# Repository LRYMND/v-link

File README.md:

## Welcome to the Boosted Moose V-Link project!

Let's face it. MMIs from the 2000s suck. This is a personal project that I started because I couldn't find a suitable aftermarket solution. I wanted to implement live vehicle data as well as AndroidAuto/Apple CarPlay in an OEM like fashion to enhance the driving experience of retro cars and give the user the ability to tinker around. The heart of this project is the open source V-Link app. It's running natively on Raspberry Pi OS which enables full support of an OS without the restrictions of 3rd party images. A custom made HAT builds the bridge between the Raspberry Pi and the car and works plug and play with the app.

To use this application you need a Raspberry Pi, the V-Link Hat (optional) and an HDMI-screen, preferably with touch support.

This project is in ongoing development. Do you want to participate, got any tips for improvement or need help?

* [Swedespeed Forum](https://www.swedespeed.com/threads/volvo-rtvi-raspberry-media-can-interface.658254/)
* [V-Link Discord Server](https://discord.gg/V4RQG6p8vM)

Feel free to fork the project. Create a new branch, commit your changes and open a pull request.

## Content

<!-- TABLE OF CONTENTS -->
<details open="open">
  <summary>Table of Contents</summary>
  <ol>
    <li><a>| App Installation</a></li>
    <li><a>| HAT Setup</a></li>
    <li><a>| Display Mod</a></li>
    <li><a>| Wiring</a></li>
    <li><a>| Audio</a></li>
    <li><a>| Disclaimer</a></li>
    <li><a>| Known Issues</a></li>
    <li><a>| Roadmap</a></li>
  </ol>
</details>

---

## 01 | App Installation

### > System Requirements:
```
Running on Raspberry Pi 3/4/5
Raspberry Pi OS 12 (Bookworm)
```

For the best user experience a RPi 4 or 5 is recommended.

---

### > Run the App:

When using the Installer everything is being set up automatically.
Before updating, please uninstall the app. (See below)

```
#Download and Install
wget "https://github.com/LRYMND/v-link/releases/download/v2.2.1/Installer.sh"
sudo chmod +x Installer.sh
sudo ./Installer.sh

#Test Hardware (Requires V-Link HAT)
python /home/$USER/v-link/HWT.py

#Execute
python /home/$USER/v-link/V-Link.py

#Advanced Options:
python /home/$USER/v-link/V-Link.py -h
```

#### In case you get an error when installing the requirements run these commands:
```
source /home/$USER/v-link/venv/bin/activate
pip install -r /home/$USER/v-link/requirements.txt
```
---

### > Run as Developer:
```
git clone https://github.com/lrymnd/v-link.git
cd v-link
python -m venv venv
source /home/$USER/v-link/venv/bin/activate
pip install -r requirements.txt
cd frontend
npm i & npm run build

cd /home/$USER/v-link/frontend
npm run vite

cd /home/$USER/v-link
python V-Link.py -h
```

```
Node v18.12.1
NPM 8.19.2
```

### > Uninstall:
```
cd ~/home/$USER/v-link/
sudo chmod +x Uninstall.sh
./Uninstall.sh
```

The Uninstall.sh script removes entries from the following location. However this is only supported from 2.2.0 onwards.
Earlier installations need to be removed manually.

```
/etc/udev/rules.d/
/etc/xdg/autostart/
/etc/network/interfaces
/home/$USER/.config
/boot/firmware/config.txt
/etc/systemd/system/
/etc/sudoers.d/
```

### > Additional functionality:

CAN and ADC data can be recorded from the chart dashboard. This data can be downloaded and evaluated with plotter.py from the /resources/tools/ folder.

```
python plotter.py $PATH_TO_JSON
```

#### Entries in /boot/firmware/config.txt:

```
[V-LINK RPi3]

#Enable GPIO 0&1
disable_poe_fan=1
force_eeprom_read=0

#Enable devicetree overlays
dtoverlay=disable-bt
enable_uart=1

dtparam=i2c_arm=on
dtoverlay=v-link
dtoverlay=mcp2515-can1,oscillator=16000000,interrupt=24
dtoverlay=mcp2515-can2,oscillator=16000000,interrupt=22

#Configure IGN logic
dtoverlay=gpio-shutdown,active_low=0,gpio_pull=up,gpio_pin=1
dtoverlay=gpio-poweroff,gpiopin=0

#No Splash on boot
disable_splash=1
```

```
[V-LINK RPi4]

#Enable GPIO 0&1
disable_poe_fan=1
force_eeprom_read=0

#Enable devicetree overlays
dtparam=spi=on
enable_uart=1
dtparam=i2c_arm=on

dtoverlay=v-link
dtoverlay=uart3
dtoverlay=mcp2515-can1,oscillator=16000000,interrupt=24
dtoverlay=mcp2515-can2,oscillator=16000000,interrupt=22

#Configure IGN logic
dtoverlay=gpio-shutdown,active_low=0,gpio_pull=up,gpio_pin=1
dtoverlay=gpio-poweroff,gpiopin=0

#No Splash on boot
disable_splash=1
```

```
[V-LINK RPi5]

#Enable GPIO 0&1
disable_poe_fan=1
force_eeprom_read=0

#Enable devicetree overlays
dtparam=spi=on
enable_uart=1
dtparam=i2c_arm=on

dtoverlay=v-link
dtparam=uart0=on
dtoverlay=uart2-pi5
dtoverlay=mcp2515-can1,oscillator=16000000,interrupt=24
dtoverlay=mcp2515-can2,oscillator=16000000,interrupt=22

#Configure IGN logic
dtoverlay=gpio-shutdown,active_low=0,gpio_pull=up,gpio_pin=1
dtoverlay=gpio-poweroff,gpiopin=0

#No Splash on boot
disable_splash=1
```
*(Don't forget to copy the custom overlays from the devicetree folder of this repository to /boot/firmware/overlays!)*

#### Further Setup:

When installing everything manually you need to set up certain features. Below you can find a list of commands to enable all necessary ports and access rights:

Enabling CAN:
```
sudo ip link set can1 type can bitrate 500000
sudo ip link set up can1

sudo ip link set can2 type can bitrate 125000
sudo ip link set up can2
```

Enabling uinput & vcan:
```
sudo modprobe uinput
sudo modprobe vcan
```

Rules for /etc/udev/rules.d/42-v-link.rules:
```
SUBSYSTEM=="usb", ATTR{idVendor}=="1314", ATTR{idProduct}=="152*", MODE="0660", GROUP="plugdev"
KERNEL=="ttyS0", MODE="0660", GROUP="plugdev"
KERNEL=="uinput", MODE="0660", GROUP="plugdev"
```

## 02 | HAT Setup

Here you can find a list of the required hardware. The V-Link HAT is currently only being sold in small batches to interested ones. If you are interested in how to get one I encourage you getting in contact via Discord! The old method which involved more hardware and technical skill is archived in the 2.0.0 branch of this repo. 

#### Hardware:
- V-Link HAT
- Raspberry Pi 3/4/5
- OEM P1 RTI Display Unit
- Carlinkit Adapter

##### CarPlay / AndroidAuto:
As of now, Carplay is working reliably on the CPC200-CCPA while AndroidAuto works better on the CPC200-CCPM Dongle. In theory, Android Auto should work on the CCPA version as well but we had mixed results. Keep this in mind when choosing your Carlinkit Adapter.

##### Raspberry Pi 3:
The Raspberry Pi 3 comes with only two UART ports. In order to use the RTI functionality you will need to place a jumper between GPIO4 and GPIO14 and short them together. Your GPIO pins won't be damaged through this and the signal arrives at the terminal of the HAT.

The V-Link HAT is attached to the Raspberry and builds the interface to the car. On this PCB you have terminals to hook up 12V, IGN, CAN etc. It also implements a safe shutdown functionality which gracefully turns off the Raspberry once ignition is off. In this state it draws a minimum of current so draining your cars battery won‘t be an issue. The LCD Touch Display and the Carlinkit Adapter are plugged into the HDMI / USB port of the raspberry and complete the setup.

## 03 | Display Mod

We currently investigate the possibility of using the OEM LCD unit, however it's recommended to go the extra mile as the proposed display has a much better resolution and supports touch input with an additional panel. The HAT comes with a dedicated 5V pin on the power terminal to run the LCD.

* [LCD Driver](https://de.aliexpress.com/item/4001175095149.html?spm=a2g0o.order_list.0.0.30e65c5fXw0Aa6&gatewayAdapt=glo2deu)
* [LCD Display](https://de.aliexpress.com/item/32835602509.html?spm=a2g0o.order_list.0.0.30e65c5fXw0Aa6&gatewayAdapt=glo2deu)
* [6.5" Touch Screen Module](https://www.ebay.de/itm/170981315406)

In order to mod your display you need to disassemble the case and take the OEM components out. Afterwards mount the new Screen in place. A custom 3D-printable bracket for easy installation can be found in the /resources folder. Be aware that the the LCDs from aliexpress come in different thicknesses. Unfortunately you can't really determine which one you're getting but if you have the option go for the slimmest variant.

## 04 | Wiring

### > 4.1 Main Connections

One way to connect the HAT to the car is to wire it to the CEM. You can solder - or better re-crimp - the wires directly to the connector. That way you aren't splicing any harnesses and the mod can be undone without damaging anything. The idea is to have an additional harness to the HAT. Keep in mind to choose appropriate diameters for you wire so they can carry the load and still fit in the connector. This is especially critical with the CAN wiring. In the future we want to make this a bit more easy.

(Borrowed from the original Volvo Electronic Wiring Diagrams)

The connections below are the bare minimum for the app to function properly on the Volvo P1 platform:

```
| Connection  | CEM Connector | Pin | HAT     |
| ----------- | ------------- | --- | ------- |
| CAN-H HS    | B             | 11  | CAN 1 H |
| CAN-L HS    | B             | 12  | CAN 1 L |
| GND         | A             | 28  | GND     |
| IGN         | A             | 17  | IGN     |
| 12V         | E             | 21  | VBAT    |
```

### > 4.2 Steering Wheel Controls (WIP)

In order to implement the steering wheel controls, you need to connect the HAT to the LIN bus of your car. The app will convert the signals from the steering wheel buttons to keyboard/mouse HID events. The easiest place to find the LIN Bus is the "ICM Connector A" behind the waterfall. Disassemble the ICM and solder a small wire to it as shown in the picture below, or add a small wire to the ICM's wiring harness.

#### Control folding mechanism:
```
| Button  | Function                  |
| ------- | ------------------------- |
| 'back'  | Hold down to close screen |
| 'enter' | Click to open screen      |
```
#### Control interface:
```
| Button     | Normal Mode | Mouse Mode         |
| ---------- | ----------- | ------------------ |
| 'Enter'    | Enter       | Left Click         |
| 'Joystick' | Navigate    | Control mouse      |
```

Holding down `Enter` button for ~2 seconds toggles between normal and mouse mode. The button mappings can be adjusted in the app.

---

### > 4.3 RTI folding mechanism

Connect Pin 4 from the RTI to the RTI pin of the HAT. You can solder directly to the RTI PCB/connector, or you can plug a DuPont wire into the connector. This can be done on the RTI side of the cable, or on the other side of the cable in the glove box. 

When ignition is turned on, the RTI screen automatically folds up. You can fold it back down through the app or the dedicated steering wheel button. Keep in mind, if your steering wheel module is not connected, you will not be able to bring the screen back up without restarting your car. The LCD will be automatically turned off in the hidden state to save power.

---

### > 4.4 Additonal Peripherals

The HAT has an input for up to 4 analog sensors. A preconfigured settings file for the Bosch 0261230482 sensor kit is provided and enables temperature and pressure readings in the app. The settings file for the analogue sensors are exposed like the CAN settings, so sensors can be added without making any changes to the code at all.

Also, to make life a bit easier, you can connect an USB extension cable to the Raspi and mount it to the removable tray behind the waterfall console. This way you can directly connect peripherals to it.

## 05 | Audio

The current solution for getting audio to work in cars that don't have a factory aux port is a [small module](https://www.tindie.com/products/justtech/aux-input-volvo-v50-s40-c30-c70-xc90/) from Lithuania.
This module is a mod for the radio to add an aux port. There is also a Bluetooth version available but since the phone is already wirelessly connected to the Carlinkit adapter dongle, an aux-cable seems pretty clean and less prone to failure.

### > Note:

This is no advertisement, just a clean and simple solution IMO. And since MOST-Bus is supported through the PiMost from ModernDayMods, it might be possible to send audio over the MOST network in the future. This is still under investigation. Feel free to join the Discord Server if you want to participate in development.

## 06 | Disclaimer

The use of this soft- and hardware is at your own risk. The author and distributor of this project is not responsible for any damage, personal injury, or any other loss resulting from the use or misuse of the setup described above. By using this setup, you agree to accept full responsibility for any consequences that arise from its use. It’s DIY after all!

## 07 | Known Issues

- In a few cases, CarPlay will connect but the stream is not visible. Restarting carplay on the phone resolves this.
- In a few cases, CAN bus communication is not working right away. Restarting the app resolves this.

## 08 | Roadmap

- [x] Exposed setting files
- [x] Fully responsive UI
- [x] Implement LIN
- [x] Implement ADC
- [x] Implement RTI
- [x] Custom hardware interface
- [x] 3D-printed display mount
- [ ] Preconfiguration for different engines
- [ ] Improved wiring to the car
- [ ] Implement DTCs
- [ ] Implement MOST

---
#### The project is inspired by the following repositories:

* [volvo-can-gauge](https://github.com/Alfaa123/Volvo-CAN-Gauge)
* [react-carplay](https://github.com/rhysmorgan134/react-carplay)
* [volvo-crankshaft](https://github.com/laurynas/volvo_crankshaft)
* [volve](https://github.com/LuukEsselbrugge/Volve)
* [volvo-vida](https://github.com/Tigo2000/Volvo-VIDA)

#### Want to join development, got any tips for improvement or need help?  

* [Swedespeed Forum](https://www.swedespeed.com/threads/volvo-rtvi-raspberry-media-can-interface.658254/)
* [V-Link Discord Server](https://discord.gg/V4RQG6p8vM)

---

|   |  |
|---|---|
| <center>(Louis)</center> | <center>(Tigo)</center> |

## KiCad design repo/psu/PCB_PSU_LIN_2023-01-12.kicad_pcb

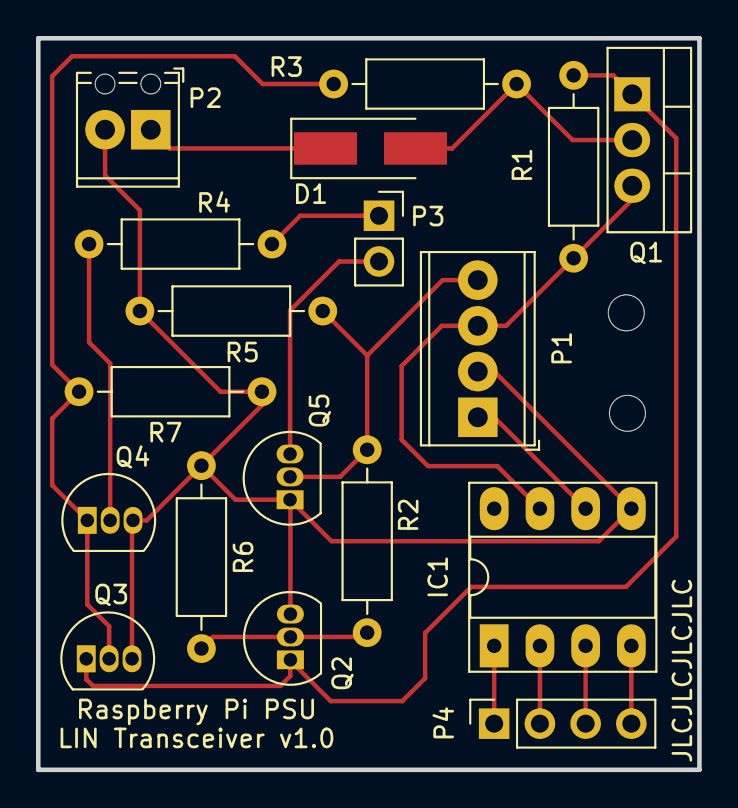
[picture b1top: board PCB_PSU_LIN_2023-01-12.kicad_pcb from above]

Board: 2 copper layers, 36.7 x 40.6 mm, 18 parts (0 on the bottom side), 12 nets.

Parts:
D1: D1; D_SMA_Handsoldering
IC1: MCP2004-E/P LIN Transceiver, 20Kbaud, Dip-8 Micro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; DIP-8_W7.62mm_Socket_LongPads
P1: TerminalBlock_Phoenix_MPT-0,5-4-2.54_1x04_P2.54mm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; TerminalBlock_Phoenix_MPT-0,5-4-2.54_1x04_P2.54mm_Horizontal
P2: TerminalBlock_Phoenix_MPT-0,5-2-2.54_1x02_P2.54mm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; TerminalBlock_Phoenix_MPT-0,5-2-2.54_1x02_P2.54mm_Horizontal
P3: PinSocket_1x02_P2.54mm_Vertical
P4: PinSocket_1x04_P2.54mm_Vertical
Q1: TO-220-3_Vertical
Q2, Q3, Q4: BC548B; TO-92L_Inline
Q5: 2N7000; TO-92L_Inline
R1, R2, R3, R4, R5, R6, R7: R_Axial_DIN0207_L6.3mm_D2.5mm_P10.16mm_Horizontal

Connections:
BATT: IC1.7, P1.3, Q1.3, R1.2
GND: IC1.5, P1.2, P2.2, Q2.3, Q3.3, Q4.3, Q5.1, R5.2, R6.1, R7.1
IGN: P1.4, Q5.2, R2.1, R5.1
LIN: IC1.6, P1.1
POWEROFF: P3.1, R4.1
Q2_2: Q2.2, R2.2, R6.2
Q3_2: Q3.2, Q4.1, R3.1, R7.2
R1_1: Q1.1, Q2.1, Q3.1, R1.1
R4_1: Q4.2, R4.2
SHUTDOWN: P3.2, Q5.3
USB_PWR: D1.2, Q1.2, R3.2
USB_PWR_DIODE: D1.1, P2.1

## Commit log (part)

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2022-12-29 Small Fixes
2022-12-30 Update environment
    Node 18.12.1, NPM 8.19.2
    React 18.2.0, Electron 22.0
    node-carplay 2.0.10
    Webpack Fixes
2022-12-30 Update README.md
    App no longer works when opening with sudo. Updated the README accordingly.
2022-12-30 Typo
2022-12-31 Fixes and enhancements.
2023-01-01 Code refactoring, small enhancements
2023-01-03 Adding SVG banner
2023-01-11 Upload Arduino code for SWM controls using LIN Bus
2023-01-11 upload MCP2004 pinout
2023-01-11 upload RTI connector
2023-01-11 upload icm connector
2023-01-11 upload icm connection
2023-01-11 Update README.md
    LIN steering wheel controls and RTI mechanism
2023-01-15 Updating Carplay component
2023-01-15 Fixes
2023-01-15 Implementing react-js-carplay
2023-01-16 Socket fix
2023-01-17 Improved readability and small fixes
2023-01-19 Including MMI deactivation
2023-01-29 More fixes
2023-02-02 Execute python on start
2023-02-07 Big refactor, update to latest node-carplay, performance enhancements
2023-02-08 Added loading animation for pairing
2023-02-08 Update README.md
    Adding some infos and fixing typos.
2023-02-08 Update README.md
    Removed menu item
2023-02-08 Visual enhancements.
2023-02-08 Cleanup.
2023-02-08 Increase version number.
2023-04-04 Implementing dash elements on carplay page.
2023-04-05 Fixing dashbar
2023-04-10 Cleaning up code, replace unsupported packages.
2023-04-12 Replaced unsupported packages
2023-04-12 Visual enhancements, small fixes
2023-06-04 Fixing the startup behaviour
2023-06-06 Fixes for Version Update
2023-06-06 Updating installer
2023-06-17 adding lambda readout
2023-06-19 Fixing Lambda readout
2023-06-20 Chart integration
2023-06-21 Implementing swipeable Dashboard and Charts
2023-06-26 Version update
2023-06-27 Code refactoring
2023-06-27 Adjusting script
2023-06-27 Script update
2023-06-29 Script adjustments
2023-07-03 Updating settings scheme
2023-07-05 New usersetting structure
2023-07-06 Responsive UI
2023-07-09 Update RTVI-Installer.sh
    Update script to 1.2.4 and fix path error
2023-07-09 Fix indentation error in dashboard script
2023-07-11 Change to electron-json-storage
2023-07-14 Custom data assignment
2023-07-14 Final implementation of flexible canbus and user settings
2023-07-15 Implement responsive can message handling
2023-07-15 Canbus adjustments
2023-07-15 Dashboard fixes
2023-07-16 Time based charts and other small improvements
2023-07-16 Adjusting linecharts
2023-07-16 Chart-timer modifications
2023-10-24 Upload PSU gerber files, kicad project file and add schematic overview
2023-10-24 Test
2023-11-15 Last commit before moving to web-app
2023-11-16 RTVI 2.0 webapp release
2023-11-17 Updated README, added Scripts, added dist
2023-11-17 Adding assets
2023-11-18 Fix dongle connect button, Add phoneWorkMode for Android
2023-11-19 Fix wrong DLC calculation
2023-11-19 Implement configurable keybindings
2023-11-19 Adding SocketIO to canbus worker
2023-11-20 Fixing canbus communication with backend
2023-11-20 Upload LIN script for steering wheel controls
2023-11-21 Upload original Arduino code for steering wheel controls
2023-11-26 Backend 2.0
2023-11-26 Refining python app
2023-11-26 Restructuring repository
2023-11-26 Removing outdated files
2023-11-26 2.0.0 Prerelease
2023-11-26 Fix bug where download can't complete, add some more CAN messages
2023-12-03 Bugfixes
2023-12-07 Webworker for car-data
2023-12-07 Small tweaks
2023-12-09 Improving CAN script
2023-12-09 Full ADC implementation
2023-12-09 .gitignore
2023-12-09 Hiding scrollbar, adding packager
2023-12-16 Adding timeout to canbus
2023-12-17 Update dependencies
2023-12-17 Frontend and backend tweaks
2023-12-21 Add support to read from a file containing sniffed LIN bytes (bin file included), convert bytes to byte literals, add missing LIN functions
2023-12-21 Updating can scripts to 2.0.0
2023-12-21 Cleanup
2023-12-28 Update Discord Link
2024-01-03 Removing venv from installer
2024-01-12 Add support to display more than two dashboard pages
2024-01-20 Racedash / Code refactoring
2024-01-26 Fully responsive frontend implementation / backend tweaks
2024-04-19 Frontend refactoring
2024-05-18 Upgrading carplay
2024-05-19 Performance improvements, updated Readme
2024-05-19 Update image
2024-05-19 Remove Splash
2024-05-19 2.1.0 V-Link Release
2024-05-20 Fixing typos
2024-05-22 Fix dtoverlays, update Readme
2024-05-24 Fixing buffer definition
2024-05-25 Updates for Pi5
2024-05-31 Update Readme, clean up repo
2024-09-24 Fix Keybindings using https://github.com/rhysmorgan134/react-carplay/compare/main...fix/keybindings
2024-10-06 Implementation of RTI and LIN via HAT
2024-10-18 modular stores
2024-11-11 push to repository
2024-11-17 Implementing RPi5 device adresses
2024-11-17 Updating .gitignore
2024-11-17 Carplay Fix
2024-11-17 Removing venv files
2024-11-17 LIN fixes
2024-11-18 Update Installer
2024-11-19 Carplay Configs
2024-11-20 2.2.0
2024-11-21 add updated installation schematic
2024-11-22 QOL improvements
2024-11-23 Keybindings for app and cleanup
2024-11-23 Fixing kiosk startup bug, UI scaling adjustments
2024-11-23 README.md aktualisieren
2024-11-25 Refactor long presses, add mouse mode, fix repeated keyboards commands. Tested in car
2024-11-26 Testing different server configurations
2024-11-26 Reset mouseSpeed on button release, cap mouse speed
2024-11-26 Update version number in Installer script and update readme
2024-12-01 Rework of lin script to time based frame handling instead of frame counting, implement enum for button and joystick states and some general improvements
2024-12-07 Improving Threading, add licence file
2024-12-07 Fix left click not working and small tweaks to joystick logic
2024-12-07 Improving Installation, adding Uninstaller
2024-12-07 Updating packager
2024-12-07 Fixing systemd service
2024-12-09 UI Refresh, Installer Fixes
2024-12-11 Temporarily disable HDMI turning off, increase default length of ChartDash
2024-12-12 Updating server dependencies
2024-12-12 Updating Uninstall.sh
2024-12-12 Unify file names
2024-12-12 Fixing file ownership
2024-12-12 Adding silent boot option
2024-12-12 Fix python-socketio version
2024-12-12 Fixing naming convention issues
2024-12-13 Fixing chart and adding record function
2024-12-13 Adding recording functionality to chart dash
2025-01-15 Implementing styled-components, initial UI rework
2025-01-16 Update container layout
2025-01-17 Convert threads to lazy instantiation, store threads themselves in shared_state, wrap rti serial in try/catch
2025-01-18 Catch array index errors in lin thread, make sure thread does not crash
2025-01-19 Finished UI conversion
2025-01-20 Improved CarPlay handling
